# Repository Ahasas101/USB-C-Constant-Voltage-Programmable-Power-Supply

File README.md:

Demonstration Video: YouTube

100 W USB-C Power Delivery Based Programmable DC Power Supply
Overview

This project implements a compact, programmable DC power supply using USB-C Power Delivery (USB-PD). It negotiates multiple voltage levels from a USB-C charger and provides a regulated, adjustable DC output suitable for electronics development and testing.

The system is built using an STM32 microcontroller, a dedicated USB-PD controller, and a high-efficiency power conversion stage. It also includes an OLED display for real-time system feedback. Both hardware and firmware are developed from scratch .

Features
USB-C Power Delivery voltage negotiation (5V, 9V, 12V, 15V, 20V)
Programmable DC output
Dual operating modes:
Direct PD Mode (fixed voltage selection)
Adjustable Output Mode (via buck converter)
Real-time voltage and current monitoring
OLED display for live system parameters
High-efficiency power conversion
Compact and portable design
Custom PCB designed in KiCad
System Architecture
Power Path

USB-C Charger → PD Controller → Power ORing → Buck Converter → Output

Control and Monitoring

Microcontroller → INA226 Sensor → OLED Display → System Monitoring and Protection

The system architecture and block diagram are described in the project document (page 4) .

Hardware Components
STM32F030C8T6 Microcontroller
CH224K USB-PD Controller
INA226 Voltage and Current Monitor
MP1584EN Buck Converter
PMOS-based Power ORing Circuit
OLED Display (I2C)
Working Modes
1. Direct PD Mode

The PD controller negotiates and outputs fixed voltage levels directly from the USB-C charger.

2. Adjustable Output Mode

The negotiated voltage is fed into a buck converter to generate a variable DC output.

PCB Design
Designed using KiCad
Includes power stage, control circuitry, sensing modules, and display interface
High-current routing and thermal considerations implemented

Author

Ahasas Yadav

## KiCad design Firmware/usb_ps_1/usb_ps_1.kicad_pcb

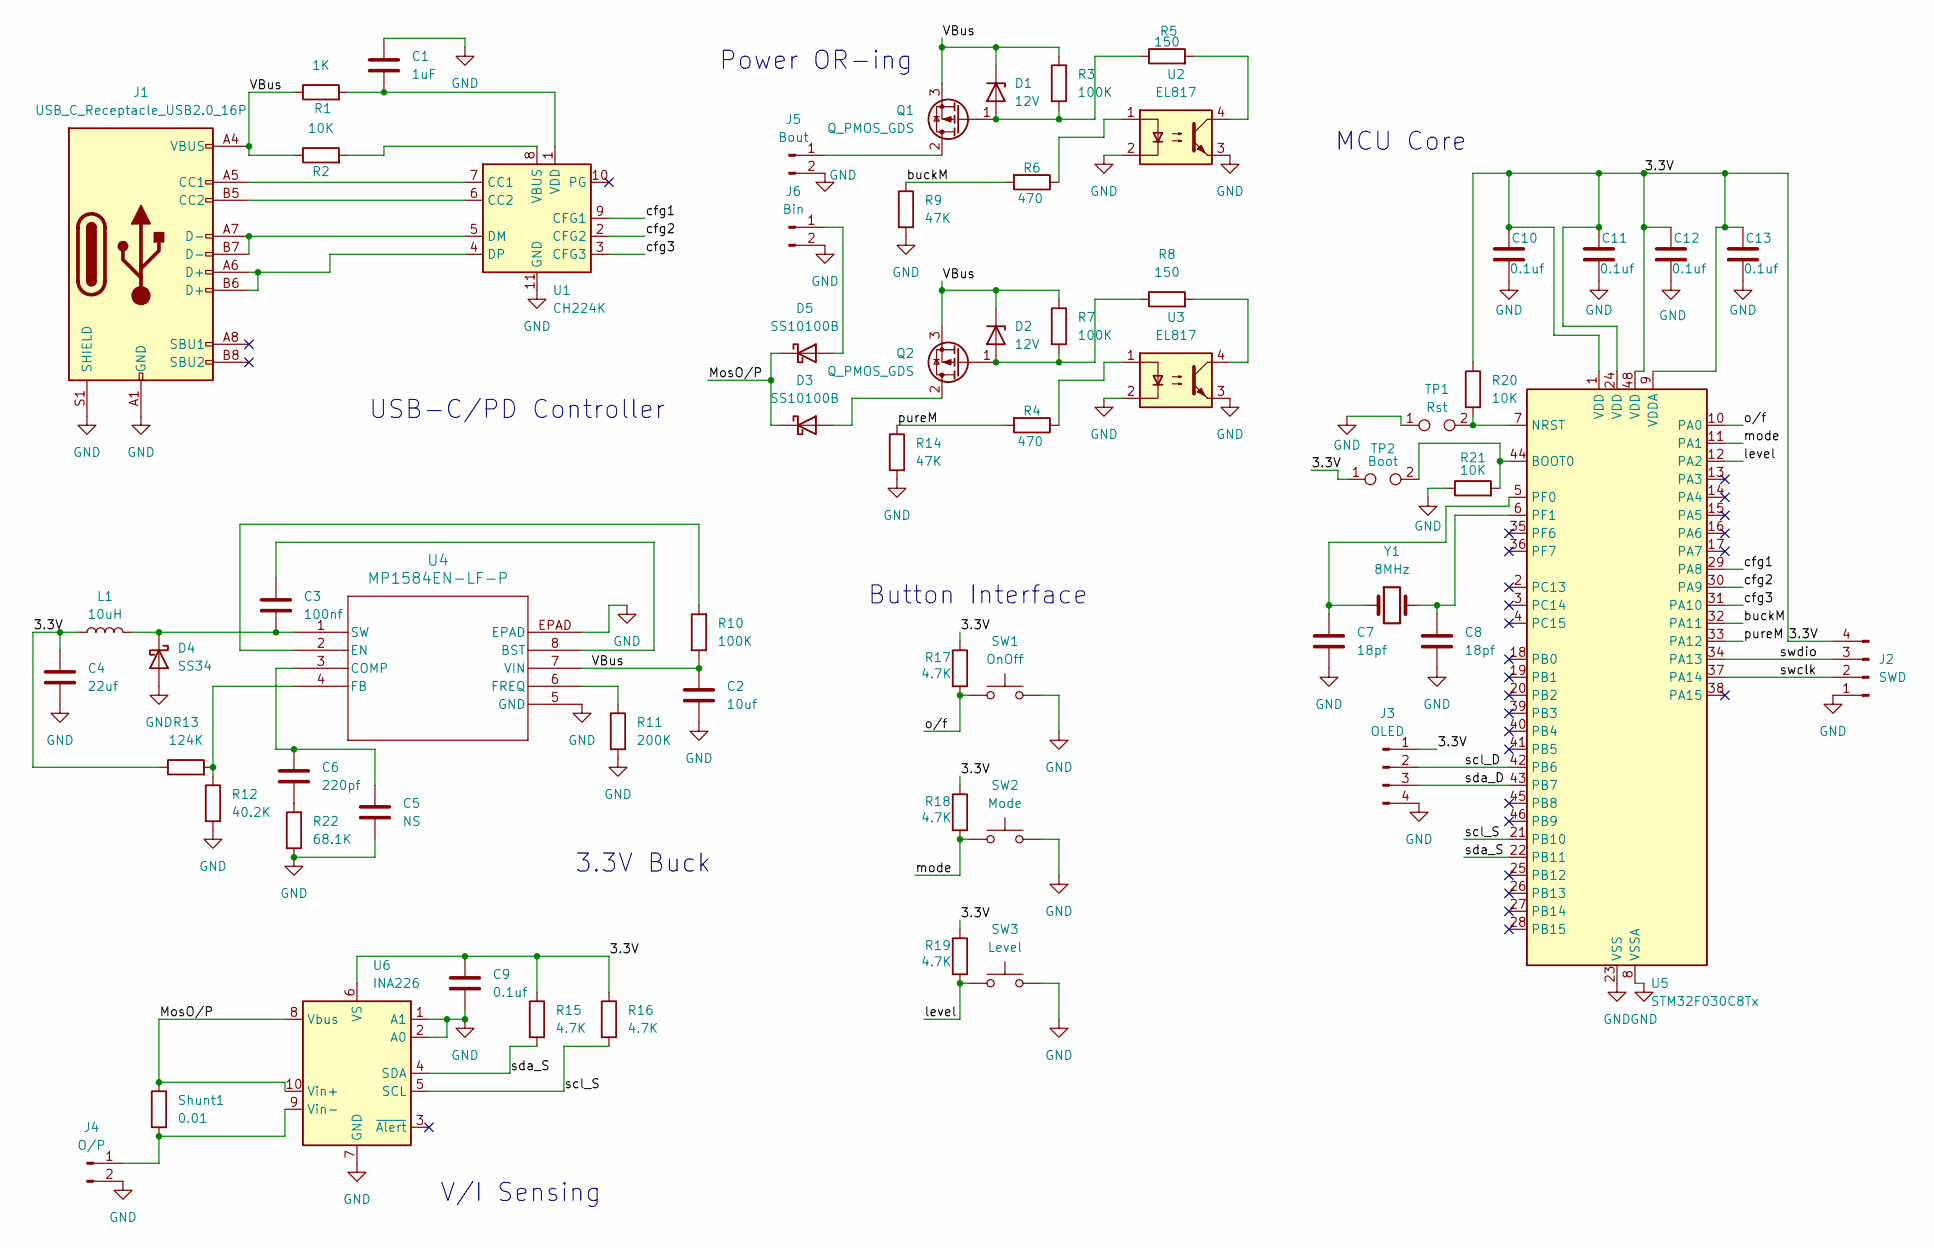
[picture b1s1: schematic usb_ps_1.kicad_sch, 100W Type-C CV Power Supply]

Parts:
C1: 1uF; C_0805_2012Metric_Pad1.18x1.45mm_HandSolder
C2: 10uf; C_0805_2012Metric_Pad1.18x1.45mm_HandSolder
C3: 100nf; C_0805_2012Metric_Pad1.18x1.45mm_HandSolder
C4: 22uf; C_0805_2012Metric_Pad1.18x1.45mm_HandSolder
C5: NS; C_0805_2012Metric_Pad1.18x1.45mm_HandSolder
C6: 220pf; C_0805_2012Metric_Pad1.18x1.45mm_HandSolder
C7, C8: 18pf; C_0805_2012Metric_Pad1.18x1.45mm_HandSolder
C9, C10, C11, C12, C13: 0.1uf; C_0805_2012Metric_Pad1.18x1.45mm_HandSolder
D1, D2: 12V; D_SMA
D3, D5: SS10100B; D_SMB
D4: SS34; D_SMA
J1: USB_C_Receptacle_USB2.0_16P; USB_C_Receptacle_G-Switch_GT-USB-7010ASV
J2: SWD; PinHeader_1x04_P2.54mm_Vertical
J3: OLED; PinHeader_1x04_P2.54mm_Vertical
J4: O/P; JST_NV_B02P-NV_1x02_P5.00mm_Vertical
J5: Bout; JST_NV_B02P-NV_1x02_P5.00mm_Vertical
J6: Bin; JST_NV_B02P-NV_1x02_P5.00mm_Vertical
L1: 10uH; L_10.4x10.4_H4.8
Q1, Q2: Q_PMOS_GDS; TO-252-3_TabPin2
R1: 1K; R_0805_2012Metric_Pad1.20x1.40mm_HandSolder
R2, R20, R21: 10K; R_0805_2012Metric_Pad1.20x1.40mm_HandSolder
R3, R7, R10: 100K; R_0805_2012Metric_Pad1.20x1.40mm_HandSolder
R4, R6: 470; R_0805_2012Metric_Pad1.20x1.40mm_HandSolder
R5, R8: 150; R_0805_2012Metric_Pad1.20x1.40mm_HandSolder
R9, R14: 47K; R_0805_2012Metric_Pad1.20x1.40mm_HandSolder
R11: 200K; R_0805_2012Metric_Pad1.20x1.40mm_HandSolder
R12: 40.2K; R_0805_2012Metric_Pad1.20x1.40mm_HandSolder
R13: 124K; R_0805_2012Metric_Pad1.20x1.40mm_HandSolder
R15, R16, R17, R18, R19: 4.7K; R_0805_2012Metric_Pad1.20x1.40mm_HandSolder
R22: 68.1K; R_0805_2012Metric_Pad1.20x1.40mm_HandSolder
SW1: OnOff; SW_SPST_B3S-1000
SW2: Mode; SW_SPST_B3S-1000
SW3: Level; SW_SPST_B3S-1000
Shunt1: 0.01; R_2512_6332Metric
TP1: Rst; C_1206_3216Metric
TP2: Boot; C_1206_3216Metric
U1: CH224K; SSOP-10-1EP_3.9x4.9mm_P1mm_EP2.1x3.3mm
U2, U3: EL817; DIP-4_W7.62mm
U4: MP1584EN-LF-P; SOIC8E_MPS_MNP
U5: STM32F030C8Tx; LQFP-48_7x7mm_P0.5mm
U6: INA226; VSSOP-10_3x3mm_P0.5mm
Y1: 8MHz; Crystal_SMD_HC49-SD

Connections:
/3.3V: C4.1, C9.1, C10.1, C11.1, C12.1, C13.1, J2.4, J3.1, L1.1, R13.1, R15.1, R16.1, R17.1, R18.1, R19.1, R20.1, TP2.1, U5.1 (VDD), U5.9 (VDDA), U5.24 (VDD), U5.48 (VDD), U6.6 (VS)
/MosO/P: D3.1 (K), D5.1 (K), Shunt1.1, U6.8 (Vbus), U6.10 (Vin+)
/VBus: C2.1, D1.1 (K), D2.1 (K), J1.A4 (VBUS), J1.A9 (VBUS), J1.B4 (VBUS), J1.B9 (VBUS), Q1.3 (S), Q2.3 (S), R1.1, R2.1, R3.1, R7.1, R10.1, U4.7 (VIN)
/buckM: R6.2, R9.1, U5.32 (PA11)
/cfg1: U1.9 (CFG1), U5.29 (PA8)
/cfg2: U1.2 (CFG2), U5.30 (PA9)
/cfg3: U1.3 (CFG3), U5.31 (PA10)
/level: R19.2, SW3.1, U5.12 (PA2)
/mode: R18.2, SW2.1, U5.11 (PA1)
/o/f: R17.2, SW1.1, U5.10 (PA0)
/pureM: R4.2, R14.1, U5.33 (PA12)
/scl_D: J3.2, U5.42 (PB6)
/scl_S: R16.2, U5.21 (PB10), U6.5 (SCL)
/sda_D: J3.3, U5.43 (PB7)
/sda_S: R15.2, U5.22 (PB11), U6.4 (SDA)
/swclk: J2.2, U5.37 (PA14)
/swdio: J2.3, U5.34 (PA13)
GND: C1.1, C2.2, C4.2, C5.2, C7.2, C8.2, C9.2, C10.2, C11.2, C12.2, C13.2, D4.2 (A), J1.A1 (GND), J1.A12 (GND), J1.B1 (GND), J1.B12 (GND), J1.S1 (SHIELD), J2.1, J3.4, J4.2, J5.2, J6.2, R9.2, R11.2, R12.2, R14.2, R21.1, R22.1, SW1.2, SW2.2, SW3.2, TP1.1, U1.11 (GND), U2.2, U2.3, U3.2, U3.3, U4.5 (GND), U4.EPAD, U5.8 (VSSA), U5.23 (VSS), U5.47 (VSS), U6.1 (A1), U6.2 (A0), U6.7 (GND)
unnamed: C6.2, R22.2
unnamed: D1.2 (A), Q1.1 (G), R3.2, R5.1
unnamed: D2.2 (A), Q2.1 (G), R7.2, R8.1
unnamed: D3.2 (A), Q2.2 (D)
unnamed: C3.2, D4.1 (K), L1.2, U4.1 (SW)
unnamed: D5.2 (A), J6.1
unnamed: J1.A5 (CC1), U1.7 (CC1)
unnamed: J1.B5 (CC2), U1.6 (CC2)
unnamed: J4.1, Shunt1.2, U6.9 (Vin-)
unnamed: J5.1, Q1.2 (D)
unnamed: R4.1, U3.1
unnamed: R5.2, U2.4
unnamed: R6.1, U2.1
unnamed: R8.2, U3.4
unnamed: J1.A7 (D-), J1.B7 (D-), U1.5 (DM)
unnamed: J1.A6 (D+), J1.B6 (D+), U1.4 (DP)
unnamed: R2.2, U1.8 (VBUS)
unnamed: C1.2, R1.2, U1.1 (VDD)
unnamed: C3.1, U4.8 (BST)
unnamed: C5.1, C6.1, U4.3 (COMP)
unnamed: R10.2, U4.2 (EN)
unnamed: R12.1, R13.2, U4.4 (FB)
unnamed: R11.1, U4.6 (FREQ)
unnamed: R21.2, TP2.2, U5.44 (BOOT0)
unnamed: R20.2, TP1.2, U5.7 (NRST)
unnamed: C7.1, U5.5 (PF0), Y1.1
unnamed: C8.1, U5.6 (PF1), Y1.2

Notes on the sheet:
Power OR-ing
MCU Core
3.3V Buck
V/I Sensing
USB-C/PD Controller
Button Interface

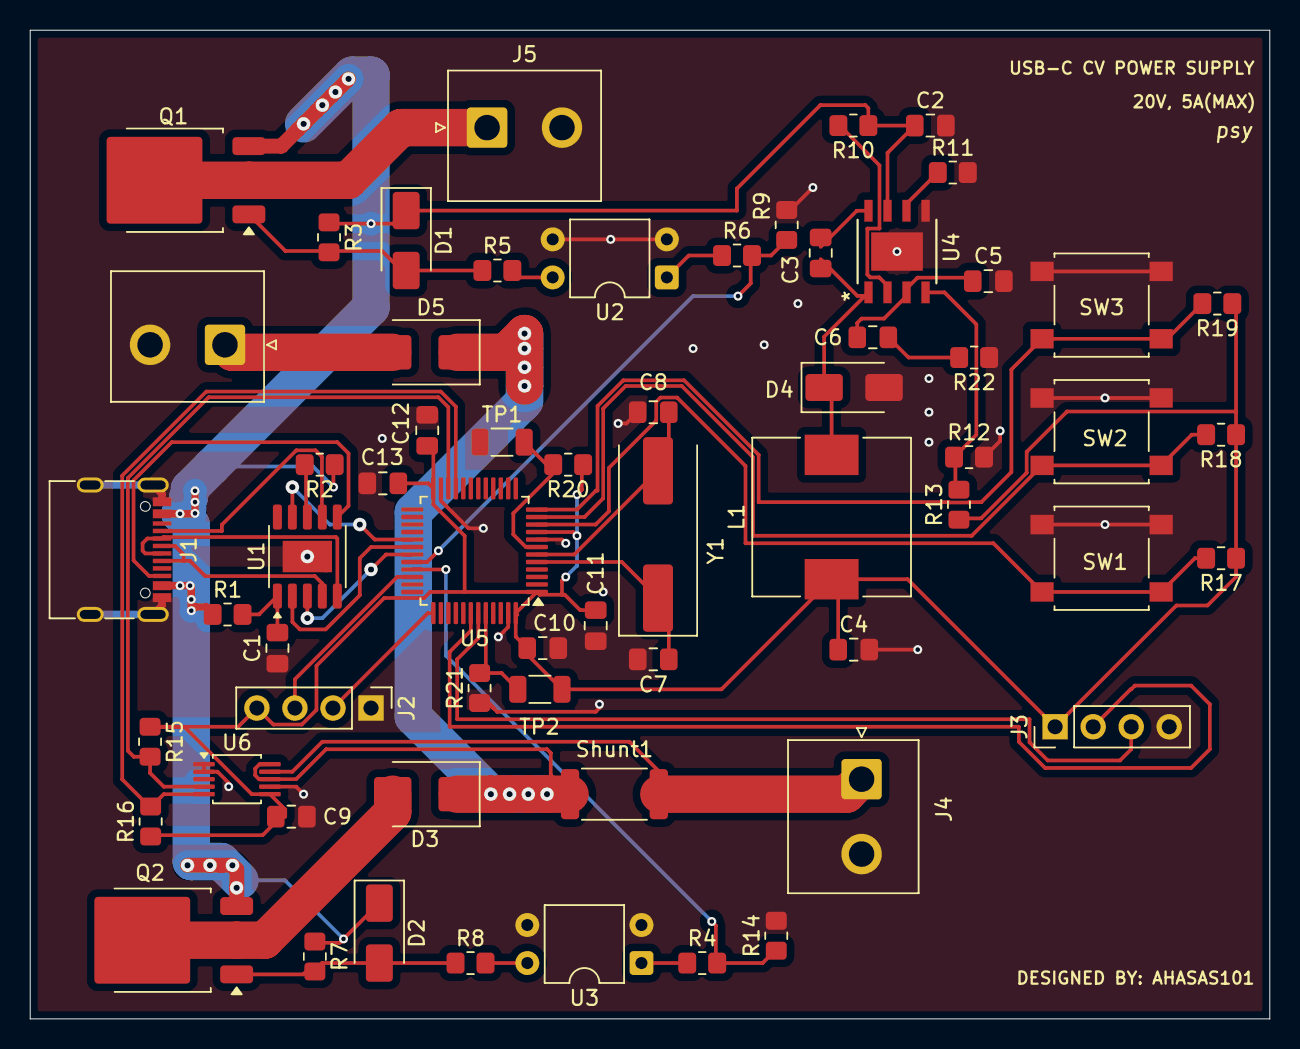
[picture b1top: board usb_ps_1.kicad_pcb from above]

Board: 2 copper layers, 82.8 x 66.0 mm, 62 parts (0 on the bottom side), 45 nets.

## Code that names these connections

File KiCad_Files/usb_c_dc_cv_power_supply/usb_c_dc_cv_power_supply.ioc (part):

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Mcu.Name=STM32F030C8Tx
Mcu.Package=LQFP48
Mcu.UserName=STM32F030C8Tx
PA0.GPIOParameters=GPIO_Label
PA0.GPIO_Label=B_1_OP_OnOff
PA0.Signal=GPXTI0
PA1.GPIOParameters=GPIO_Label
PA1.GPIO_Label=B_3_Mode
PA1.Signal=GPXTI1
PA10.GPIOParameters=GPIO_Label
PA10.GPIO_Label=cfg3
PA10.Signal=GPIO_Output
PA11.GPIOParameters=GPIO_Label
PA11.GPIO_Label=buck_mosfet
PA11.Signal=GPIO_Output
PA12.GPIOParameters=GPIO_Label
PA12.GPIO_Label=pure_mosfet
PA12.Signal=GPIO_Output
PA13.Mode=Serial_Wire
PA13.Signal=SYS_SWDIO
PA14.Mode=Serial_Wire
PA14.Signal=SYS_SWCLK
PA2.GPIOParameters=GPIO_Label
PA2.GPIO_Label=B_2_VL
PA2.Signal=GPXTI2
PA8.GPIOParameters=GPIO_Label
PA8.GPIO_Label=cfg1
PA8.Signal=GPIO_Output
PA9.GPIOParameters=GPIO_Label
PA9.GPIO_Label=cfg2
PA9.Signal=GPIO_Output
PB10.Mode=I2C
PB10.Signal=I2C2_SCL
PB11.Mode=I2C
PB11.Signal=I2C2_SDA
PB6.Mode=I2C
PB6.Signal=I2C1_SCL
PB7.Mode=I2C
PB7.Signal=I2C1_SDA
board=custom

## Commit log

2026-04-27 Bugs Fixed
2026-04-27 added readme.md
